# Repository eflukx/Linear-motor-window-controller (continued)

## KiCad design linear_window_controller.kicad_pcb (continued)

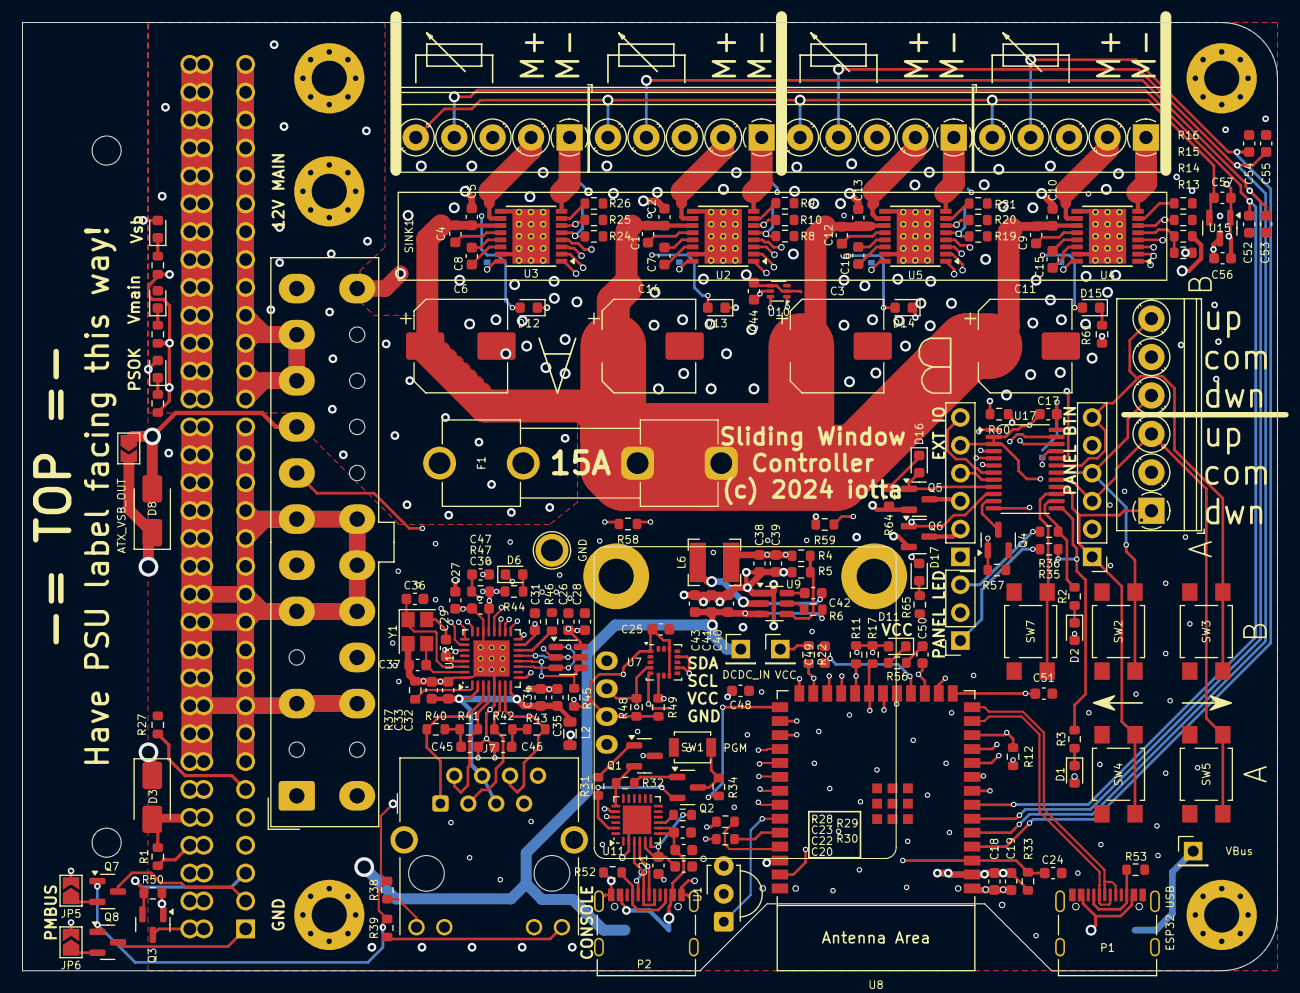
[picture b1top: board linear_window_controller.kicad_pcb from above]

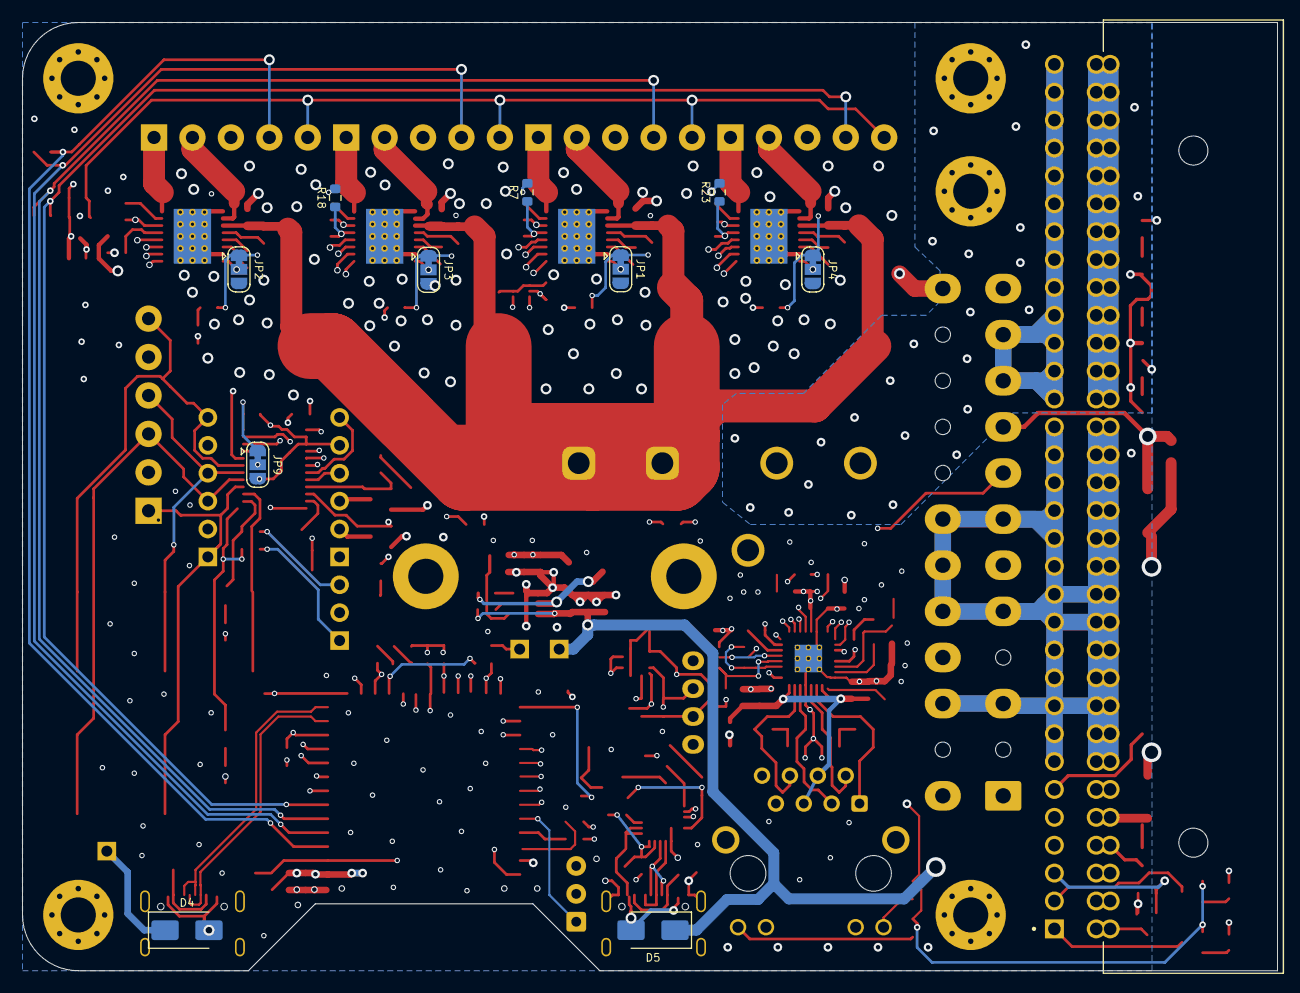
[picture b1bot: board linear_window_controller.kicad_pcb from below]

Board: 4 copper layers, 114.3 x 86.4 mm, 201 parts (11 on the bottom side), 159 nets.

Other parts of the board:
C38, C39: 22u; C_0603_1608Metric
C40: 100n; C_0603_1608Metric
C41: 10u; C_0603_1608Metric
R4: 33k; R_0603_1608Metric
R5: 10k; R_0603_1608Metric
SINK1: heatsink_window_controller_70x8mm

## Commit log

2024-02-01 Linear quad/octa motor slide Window controller, featuring absolute position feedback control, motor current monitoring using a ESP32-S3 hi performance controller.
    Vordert al best een beetje, dus tijd voor een eerste commit :)
    https://www.youtube.com/watch?v=r6Ve47lJ-PA
2024-03-07 Finish most of the routing, add DM9051 fast ethernet controller
2024-03-07 Commit project-local 3d files
2024-03-07 Add relevant documentation
2024-03-08 Finalize routing and cleanup. Change DCDC to TPS562200 Add some more things (e.g. power monitoring LEDs) Update some partno's in BOM
2024-03-09 Update schematic layout and fully update BOM for production
2024-03-09 Update edge connector orientation (correct bottom mount)
2024-03-12 Add TMP100 and LIS3DH sensors, update board layout, teardrops
2024-08-06 Update schematic with (resistor) values and informative text
2024-08-15 Change ethernet jack to the (much) more common Hanrun HR911105A (in stead of what was still in my bench drawer) Add smoothing caps on potentiometer output Add separate voltage regulation for the pote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
2024-08-16 Add channel indication LEDs Add external IO (2 inputs/low power IO, 2 high power OD outputs for e.g. magnetic locks) Swap PCF8574 for PCA9555 16 bit iot expander Add heatsink to board (3D) Add PDF fi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
2024-08-19 Update PCB to reflect the v2.x update Included PMbus voltage shifter (5V <-> 3.3V)
